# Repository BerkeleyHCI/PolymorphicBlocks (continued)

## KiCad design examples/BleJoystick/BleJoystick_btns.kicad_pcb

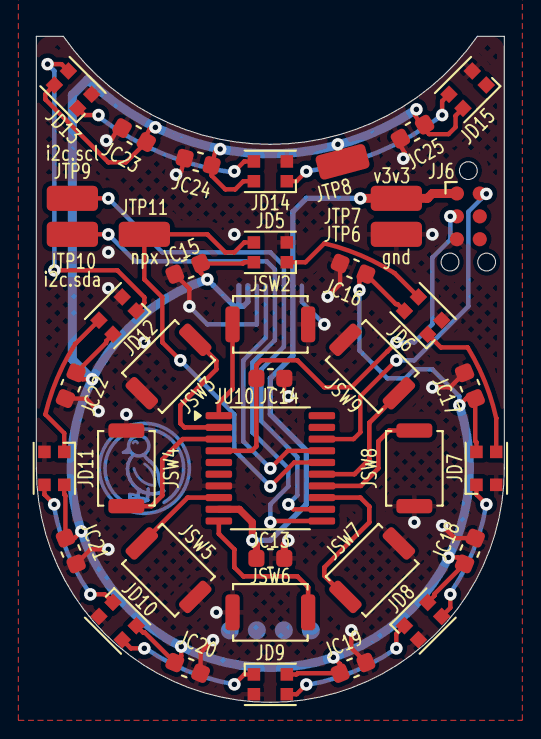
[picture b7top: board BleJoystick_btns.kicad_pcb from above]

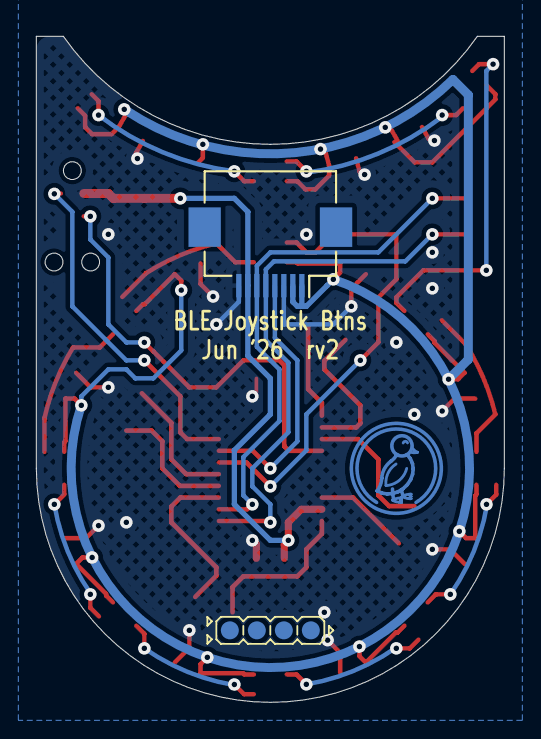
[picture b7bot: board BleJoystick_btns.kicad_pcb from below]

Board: 2 copper layers, 26.0 x 37.0 mm, 42 parts (2 on the bottom side), 27 nets.

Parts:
JC13: btns.ioe.vdd_cap; C_0603_1608Metric
JC14: btns.ioe.reset_cap; C_0603_1608Metric
JC15: btns.npx_dpad.led[0].cap; C_0603_1608Metric
JC16: btns.npx_dpad.led[1].cap; C_0603_1608Metric
JC17: btns.npx_dpad.led[2].cap; C_0603_1608Metric
JC18: btns.npx_dpad.led[3].cap; C_0603_1608Metric
JC19: btns.npx_dpad.led[4].cap; C_0603_1608Metric
JC20: btns.npx_dpad.led[5].cap; C_0603_1608Metric
JC21: btns.npx_dpad.led[6].cap; C_0603_1608Metric
JC22: btns.npx_dpad.led[7].cap; C_0603_1608Metric
JC23: btns.npx_js.led[0].cap; C_0603_1608Metric
JC24: btns.npx_js.led[1].cap; C_0603_1608Metric
JC25: btns.npx_js.led[2].cap; C_0603_1608Metric
JD5: btns.npx_dpad.led[0].device; LED_WS2812B-2020_PLCC4_2.0x2.0mm
JD6: btns.npx_dpad.led[1].device; LED_WS2812B-2020_PLCC4_2.0x2.0mm
JD7: btns.npx_dpad.led[2].device; LED_WS2812B-2020_PLCC4_2.0x2.0mm
JD8: btns.npx_dpad.led[3].device; LED_WS2812B-2020_PLCC4_2.0x2.0mm
JD9: btns.npx_dpad.led[4].device; LED_WS2812B-2020_PLCC4_2.0x2.0mm
JD10: btns.npx_dpad.led[5].device; LED_WS2812B-2020_PLCC4_2.0x2.0mm
JD11: btns.npx_dpad.led[6].device; LED_WS2812B-2020_PLCC4_2.0x2.0mm
JD12: btns.npx_dpad.led[7].device; LED_WS2812B-2020_PLCC4_2.0x2.0mm
JD13: btns.npx_js.led[0].device; LED_WS2812B-2020_PLCC4_2.0x2.0mm
JD14: btns.npx_js.led[1].device; LED_WS2812B-2020_PLCC4_2.0x2.0mm
JD15: btns.npx_js.led[2].device; LED_WS2812B-2020_PLCC4_2.0x2.0mm
JJ6: btns.ioe.sdi; Tag-Connect_TC2030-IDC-NL_2x03_P1.27mm_Vertical
JJ8: btns.conn; Hirose_FH12-8S-0.5SH_1x08-1MP_P0.50mm_Horizontal
JSW2: btns.sw[0]; SW_Push_SPST_NO_Alps_SKRK
JSW3: btns.sw[1]; SW_Push_SPST_NO_Alps_SKRK
JSW4: btns.sw[2]; SW_Push_SPST_NO_Alps_SKRK
JSW5: btns.sw[3]; SW_Push_SPST_NO_Alps_SKRK
JSW6: btns.sw[4]; SW_Push_SPST_NO_Alps_SKRK
JSW7: btns.sw[5]; SW_Push_SPST_NO_Alps_SKRK
JSW8: btns.sw[6]; SW_Push_SPST_NO_Alps_SKRK
JSW9: btns.sw[7]; SW_Push_SPST_NO_Alps_SKRK
JTP6: gnd; TestPoint_TE_RCT_0805
JTP7: v3v3; TestPoint_TE_RCT_0805
JTP8: vbat; TestPoint_TE_RCT_0805
JTP9: i2c.scl; TestPoint_TE_RCT_0805
JTP10: i2c.sda; TestPoint_TE_RCT_0805
JTP11: npx; TestPoint_TE_RCT_0805
JU10: btns.ioe.ic; TSSOP-20_4.4x6.5mm_P0.65mm
duck: G***; Symbol_Duckling

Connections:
Jbtns_btns.gnd: JC13.2, JC14.2, JC15.2, JC16.2, JC17.2, JC18.2, JC19.2, JC20.2, JC21.2, JC22.2, JC23.2, JC24.2, JC25.2, JD5.2, JD6.2, JD7.2, JD8.2, JD9.2, JD10.2, JD11.2, JD12.2, JD13.2, JD14.2, JD15.2, JJ6.5, JJ8.3, JJ8.8, JSW2.2, JSW3.2, JSW4.2, JSW5.2, JSW6.2, JSW7.2, JSW8.2, JSW9.2, JTP6.1, JU10.7
Jbtns_btns.i2c.scl: JJ8.6, JTP9.1, JU10.12
Jbtns_btns.i2c.sda: JJ8.5, JTP10.1, JU10.11
Jbtns_btns.io0: JJ8.4, JU10.17
Jbtns_btns.ioe.ic.nrst: JC14.1, JJ6.3, JU10.4
Jbtns_btns.ioe.ic.swio: JJ6.2, JU10.18
Jbtns_btns.npx_dpad.dout: JD12.1, JD13.3
Jbtns_btns.npx_dpad.led[0].dout: JD5.1, JD6.3
Jbtns_btns.npx_dpad.led[1].dout: JD6.1, JD7.3
Jbtns_btns.npx_dpad.led[2].dout: JD7.1, JD8.3
Jbtns_btns.npx_dpad.led[3].dout: JD8.1, JD9.3
Jbtns_btns.npx_dpad.led[4].dout: JD9.1, JD10.3
Jbtns_btns.npx_dpad.led[5].dout: JD10.1, JD11.3
Jbtns_btns.npx_dpad.led[6].dout: JD11.1, JD12.3
Jbtns_btns.npx_js.led[0].dout: JD13.1, JD14.3
Jbtns_btns.npx_js.led[1].dout: JD14.1, JD15.3
Jbtns_btns.npx_tp.io: JD5.3, JTP11.1, JU10.16
Jbtns_btns.pwr: JC13.1, JJ6.1, JJ8.7, JTP7.1, JU10.9
Jbtns_btns.sw[0].out: JSW2.1, JU10.1
Jbtns_btns.sw[1].out: JSW3.1, JU10.2
Jbtns_btns.sw[2].out: JSW4.1, JU10.3
Jbtns_btns.sw[3].out: JSW5.1, JU10.8
Jbtns_btns.sw[4].out: JSW6.1, JU10.10
Jbtns_btns.sw[5].out: JSW7.1, JU10.13
Jbtns_btns.sw[6].out: JSW8.1, JU10.14
Jbtns_btns.sw[7].out: JSW9.1, JU10.15
Jbtns_btns.vbat: JC15.1, JC16.1, JC17.1, JC18.1, JC19.1, JC20.1, JC21.1, JC22.1, JC23.1, JC24.1, JC25.1, JD5.4, JD6.4, JD7.4, JD8.4, JD9.4, JD10.4, JD11.4, JD12.4, JD13.4, JD14.4, JD15.4, JJ8.1, JJ8.2, JTP8.1

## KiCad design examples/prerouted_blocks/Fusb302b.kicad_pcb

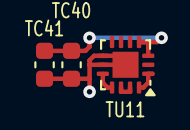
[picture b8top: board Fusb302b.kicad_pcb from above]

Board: 2 copper layers, 3 parts (0 on the bottom side), 5 nets.

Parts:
TC40: pd.vdd_cap[0]; C_0603_1608Metric
TC41: pd.vdd_cap[1]; C_0603_1608Metric
TU11: pd.ic; WQFN-14-1EP_2.5x2.5mm_P0.5mm_EP1.45x1.45mm

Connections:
Tgnd: TC40.2, TC41.2, TU11.8, TU11.9, TU11.15
Tpd.ic.vconn: TU11.12, TU11.13
Tusb.cc.cc1: TU11.10, TU11.11
Tusb.cc.cc2: TU11.1, TU11.14
Tv3v3: TC40.1, TC41.1, TU11.3, TU11.4

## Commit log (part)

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2026-06-14 backbone floorplanning
2026-06-14 magnetometer cleanup
2026-06-15 drc cleanish
2026-06-15 polishing
2026-06-15 drc exclude updates
2026-06-15 socket-tab pair
2026-06-15 done
2026-06-16 load switch and routing wip
2026-06-16 clean
2026-06-16 finally done probably
2026-06-17 cleaned up routing
2026-06-17 regenerate netlists, fix deprecations
2026-06-17 fixes
2026-06-17 Example boards layout and library fixes (#519)
    Board layouts for the IoT fan / addressable strip driver, BLE joystick
    v2, and keyboard.
    Library changes:
    - Add PMOS only load switch
    - Changes the keyboard switchmatrix args to be ncols first (x dimension)
    and for internal switch ordering (which matters for refdesing) to
2026-06-18 wip ethernet terminations
2026-06-18 create bundled ethernet link
2026-06-18 iterate on naming
2026-06-20 poe controller
2026-06-20 jumper
2026-06-20 ready for layout, probably
2026-06-20 wip layout
2026-06-20 floorplanning
2026-06-21 cleanup routing
2026-06-21 Fix fusb302b vdd cap value
2026-06-22 wip almost done
2026-06-22 update reference netlists
2026-06-22 fix types
2026-06-22 fix naming, ground unused pin
2026-06-22 Ethernet + non-isolated PoE example (#523)
    Changes the FLIR example to be PoE + Ethernet using W5000. Adds Ethernet
    port / link types in the example (for now, until validated in hardware).
    Completed board layout. Really more of a parts test omnibus board, it's
    not a pretty layout. In retrospect, this should have been a four-layer
    board.
    Other changes:
2026-06-22 wip LDO changes
2026-06-23 subboard prefixing
2026-06-23 ams1117
2026-06-23 part selection optimization
2026-06-23 cleaning
2026-06-23 generate netlist
2026-06-23 cleanup
2026-06-23 refactor jlc to module script
2026-06-23 placement data
2026-06-24 update netlists
2026-06-24 Example board modifications + final (hopefully) layouts (#526)
    Changes:
    - Change diode drop of soft power gate to up to 0.6V, to allow JLC basic
    parts
    - Move refdes prefixing into the netlist emitter. Add subboard prefix to
    the emitter, to allow unique nets under panelization.
    - Add QMC5883P, which seems to have superseded the QMC5883L
2026-06-24 Make CAN passive
2026-06-24 cleanup deprecations
2026-06-24 API pruning
2026-06-24 clean up cc port
2026-06-24 wip usb passive refactor
2026-06-24 one example builds
2026-06-24 refactor mciros
2026-06-25 fix usb (and generally passive) pinning
2026-06-25 Rename current_drawn -> current_draw
2026-06-25 voltage renaming for analog
2026-06-25 wip out cleanup
2026-06-25 wip rename voltages
2026-06-25 cleanup type errors
2026-06-25 blacken
2026-06-25 Rename cleanups, make some budle ports Passive (#527)
    - Changes USB, CAN differential, and USB CC bundles to contain Passive
    typed Ports, since they have special signaling requirements and are not
    compatible with Digital ports.
    - Renames voltage_out -> voltage, signal_out -> signal, with deprecation
    pathway.
    - Fixes a bug where the IoController pin assigner would ignore Passive
2026-06-28 split out
2026-06-28 streamlining
2026-06-28 cleanup categorization
2026-06-29 generate mixin data
2026-06-29 Add is_mixin to IR (#529)
2026-06-29 Update figures
